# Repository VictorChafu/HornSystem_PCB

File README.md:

# HornSystem_PCB
Desarrollo de hardware en Kicad

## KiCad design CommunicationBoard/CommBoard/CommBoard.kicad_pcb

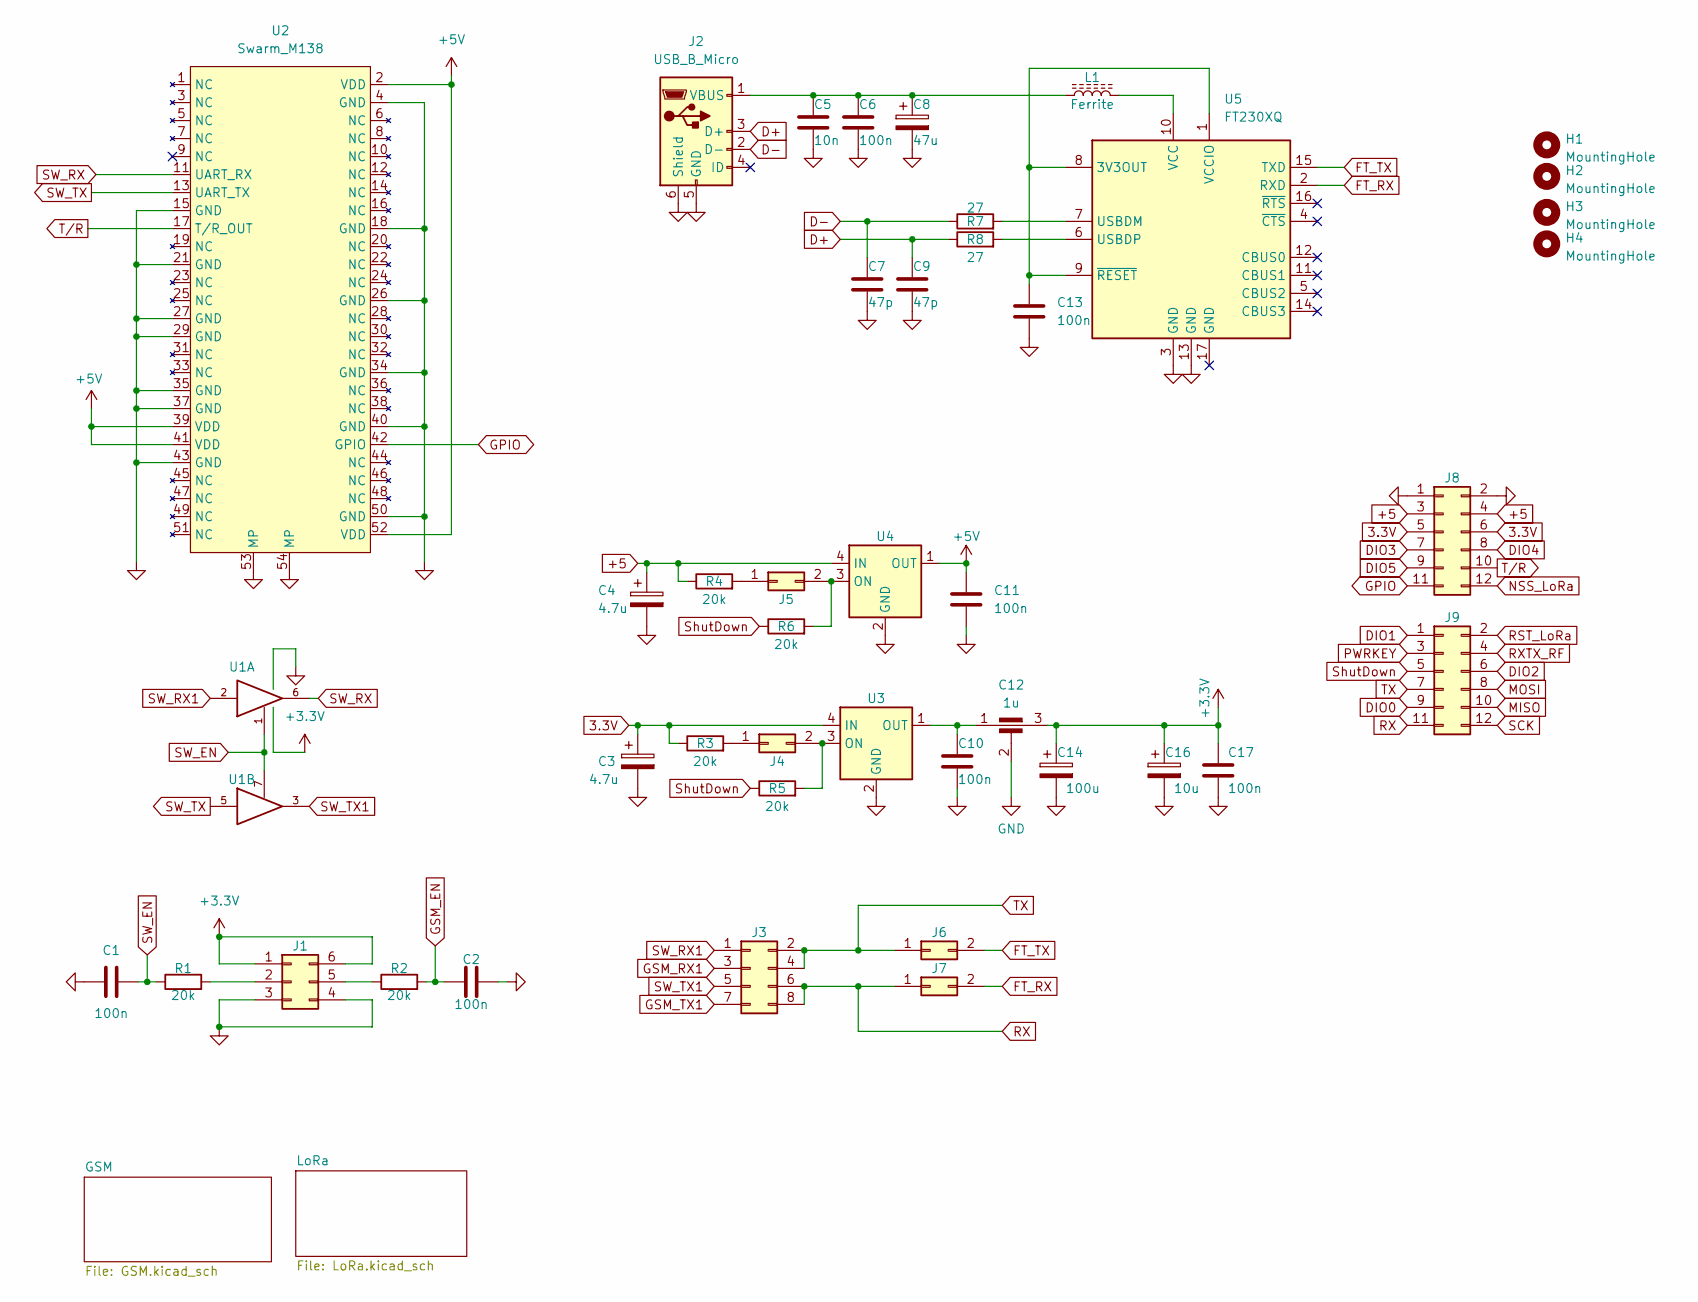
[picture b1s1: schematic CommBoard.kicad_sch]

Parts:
C1, C2, C6, C10, C11, C13, C17: 100n; C_0402_1005Metric
C3, C4: 4.7u; CP_Elec_6.3x5.2
C5: 10n; C_0402_1005Metric
C7, C9: 47p; C_0402_1005Metric
C8: 47u; CP_Elec_6.3x5.2
C12: 1u; YFF31HC
C14: 100u; CP_Elec_6.3x5.2
C16: 10u; CP_Elec_6.3x5.2
H1, H2, H3, H4: MountingHole; MountingHole_2.5mm
J1: Conn_02x03_Counter_Clockwise; PinHeader_2x03_P2.54mm_Vertical
J2: USB_B_Micro; USB_Micro-B_Molex_47346-0001
J3: Conn_02x04_Top_Bottom; PinHeader_2x04_P2.54mm_Vertical
J4, J5, J6, J7: Conn_02x01; PinHeader_2x01_P2.54mm_Vertical
J8, J9: Conn_02x06_Odd_Even; PinHeader_2x06_P2.54mm_Vertical
L1: Ferrite; L_0402_1005Metric
R1, R2, R3, R4, R5, R6: 20k; R_0402_1005Metric
R7, R8: 27; R_0402_1005Metric
U1: 74LVC2G126; VSSOP-8_2.4x2.1mm_P0.5mm
U2: Swarm_M138; BUS_PCI_Express_Mini_Dual
U3, U4: SiP35508; SOT-23-6
U5: FT230XQ; SSOP-16_3.9x4.9mm_P0.635mm

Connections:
3.3V: C3.1, J8.5, J8.6, R3.1, U3.4 (IN)
+3V3: C12.3, C14.1, C16.1, C17.1, J1.1, J1.6, U1.8 (VCC); also elsewhere on the board
+5: C4.1, J8.3, J8.4, R4.1, U4.4 (IN)
+5V: C11.1, U2.2 (VDD), U2.39 (VDD), U2.41 (VDD), U2.52 (VDD), U4.1 (OUT); also elsewhere on the board
D+: C9.1, J2.3 (D+), R8.1
D-: C7.1, J2.2 (D-), R7.1
DIO0: J9.9; also elsewhere on the board
DIO1: J9.1; also elsewhere on the board
DIO2: J9.6; also elsewhere on the board
DIO3: J8.7; also elsewhere on the board
DIO4: J8.8; also elsewhere on the board
DIO5: J8.9; also elsewhere on the board
FT_RX: J7.2, U5.2 (RXD)
FT_TX: J6.2, U5.15 (TXD)
GND: C1.1, C2.2, C3.2, C4.2, C5.2, C6.2, C7.2, C8.2, C9.2, C10.2, C11.2, C12.2, C13.2, C14.2, C16.2, C17.2, J1.3, J1.4, J2.5 (GND), J2.6 (Shield), J8.1, J8.2, U1.4 (GND), U2.4 (GND), U2.15 (GND), U2.18 (GND), U2.21 (GND), U2.26 (GND), U2.27 (GND), U2.29 (GND), U2.34 (GND), U2.35 (GND), U2.37 (GND), U2.40 (GND), U2.43 (GND), U2.50 (GND), U2.53 (MP), U2.54 (MP), U3.2 (GND), U3.5 (GND), U4.2 (GND), U4.5 (GND), U5.3 (GND), U5.13 (GND); also elsewhere on the board
GPIO: J8.11, U2.42 (GPIO)
GSM_EN: C2.1, R2.2; also elsewhere on the board
GSM_RX1: J3.3; also elsewhere on the board
GSM_TX1: J3.7; also elsewhere on the board
MISO: J9.10; also elsewhere on the board
MOSI: J9.8; also elsewhere on the board
NSS_LoRa: J8.12; also elsewhere on the board
unnamed: C5.1, C6.1, C8.1, J2.1 (VBUS), L1.1
unnamed: C10.1, C12.1, U3.1 (OUT)
unnamed: C13.1, U5.1 (VCCIO), U5.8 (3V3OUT), U5.9 (~RESET)
unnamed: J1.2, R1.2
unnamed: J1.5, R2.1
unnamed: J4.1, R3.2
unnamed: J4.2, R5.2, U3.3 (ON)
unnamed: J5.1, R4.2
unnamed: J5.2, R6.2, U4.3 (ON)
unnamed: L1.2, U5.10 (VCC)
unnamed: R7.2, U5.7 (USBDM)
unnamed: R8.2, U5.6 (USBDP)
PWRKEY: J9.3; also elsewhere on the board
RST_LoRa: J9.2; also elsewhere on the board
RX: J3.6, J3.8, J7.1, J9.11
RXTX_RF: J9.4; also elsewhere on the board
SCK: J9.12; also elsewhere on the board
SW_EN: C1.2, R1.1, U1.1, U1.7
SW_RX: U1.6, U2.11 (UART_RX)
SW_RX1: J3.1, U1.2
SW_TX: U1.5, U2.13 (UART_TX)
SW_TX1: J3.5, U1.3
ShutDown: J9.5, R5.1, R6.1
TX: J3.2, J3.4, J6.1, J9.7
T/R: J8.10, U2.17 (T/R_OUT)

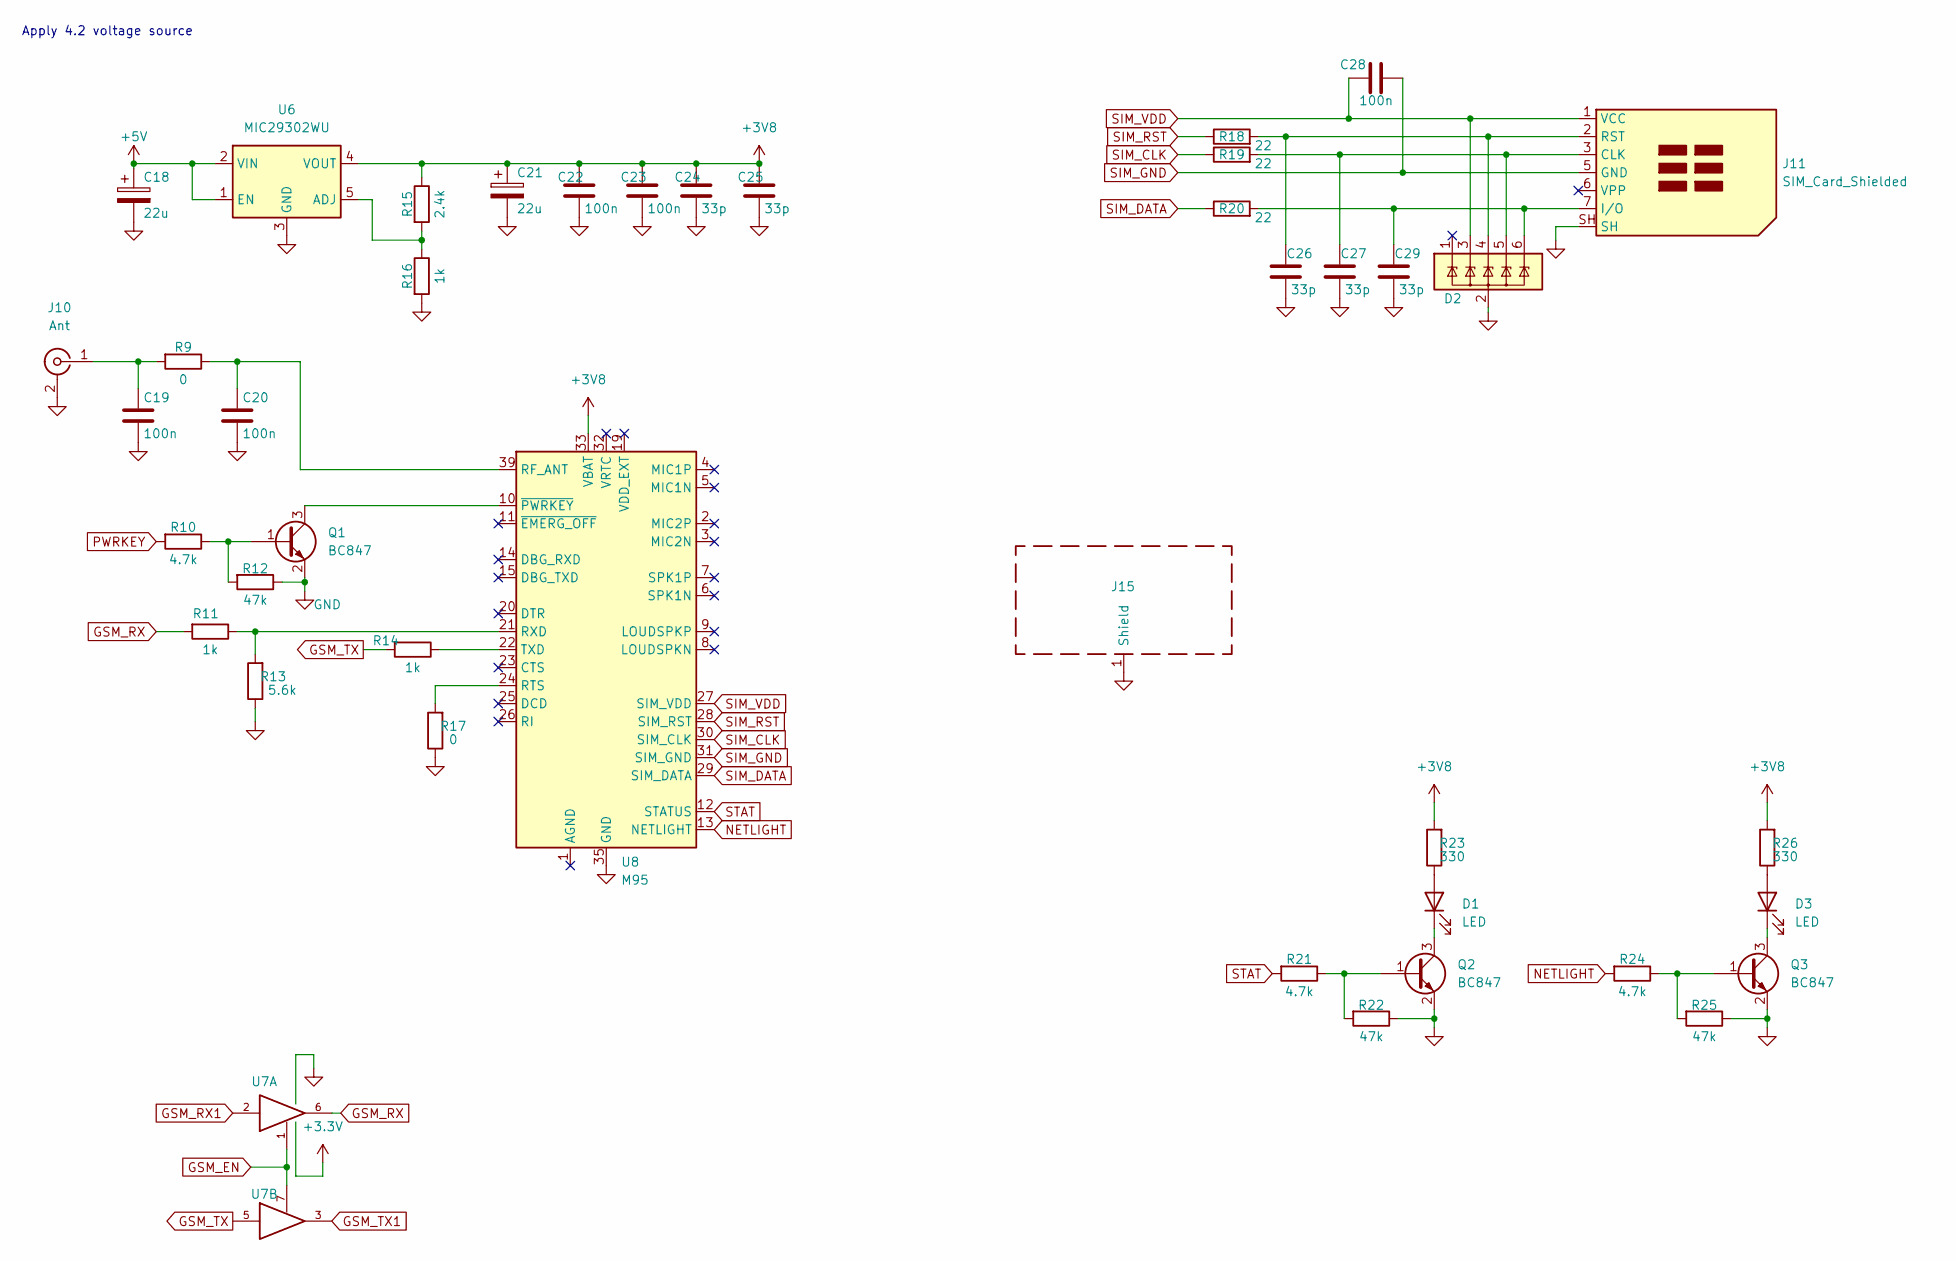
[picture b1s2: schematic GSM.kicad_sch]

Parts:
C18, C21: 22u; CP_Elec_6.3x5.2
C19, C20, C22, C23, C28: 100n; C_0402_1005Metric
C24, C25, C26, C27, C29: 33p; C_0402_1005Metric
D1, D3: LED; LED_0805_2012Metric
D2: ESDA6V1-5SC6; SOT-23-6
J10: Ant; U.FL_Hirose_U.FL-R-SMT-1_Vertical
J11: SIM_Card_Shielded; microSIM_JAE_SF53S006VCBR2000
J15: RFShield_OnePiece; Laird_Technologies_BMI-S-205-F_38.10x25.40mm
Q1, Q2, Q3: BC847; SOT-23
R9: 0; R_0402_1005Metric
R10, R21, R24: 4.7k; R_0402_1005Metric
R11, R14: 1k; R_0402_1005Metric
R12, R22, R25: 47k; R_0402_1005Metric
R13: 5.6k; R_0402_1005Metric
R15: 2.4k; R_0805_2012Metric
R16: 1k; R_0805_2012Metric
R17: 0; R_0805_2012Metric
R18, R19, R20: 22; R_0402_1005Metric
R23, R26: 330; R_0402_1005Metric
U6: MIC29302WU; TO-263-5_TabPin3
U7: 74LVC2G126; VSSOP-8_2.4x2.1mm_P0.5mm
U8: M95; Quectel_M95

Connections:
+3V3: U7.8 (VCC); also elsewhere on the board
+3V8: C21.1, C22.1, C23.1, C24.1, C25.1, R15.1, R23.2, R26.2, U6.4 (VOUT), U8.33 (VBAT), U8.34 (VBAT)
+5V: C18.1, U6.1 (EN), U6.2 (VIN); also elsewhere on the board
GND: C18.2, C19.2, C20.2, C21.2, C22.2, C23.2, C24.2, C25.2, C26.2, C27.2, C29.2, D2.2 (GND), J10.2 (Ext), J11.SH, J15.1 (Shield), Q1.2 (E), Q2.2 (E), Q3.2 (E), R12.1, R13.1, R16.2, R17.1, R22.1, R25.1, U6.3 (GND), U7.4 (GND), U8.35 (GND), U8.36 (GND), U8.37 (GND), U8.38 (GND), U8.40 (GND); also elsewhere on the board
GSM_EN: U7.1, U7.7; also elsewhere on the board
GSM_RX: R11.2, U7.6
GSM_RX1: U7.2; also elsewhere on the board
GSM_TX: R14.2, U7.5
GSM_TX1: U7.3; also elsewhere on the board
NETLIGHT: R24.2, U8.13 (NETLIGHT)
unnamed: C19.1, J10.1 (In), R9.2
unnamed: C20.1, R9.1, U8.39 (RF_ANT)
unnamed: C26.1, D2.4 (IO3), J11.2 (RST), R18.2
unnamed: C27.1, D2.5 (IO4), J11.3 (CLK), R19.2
unnamed: C29.1, D2.6 (IO5), J11.7 (I/O), R20.2
unnamed: D1.1 (K), Q2.3 (C)
unnamed: D1.2 (A), R23.1
unnamed: D3.1 (K), Q3.3 (C)
unnamed: D3.2 (A), R26.1
unnamed: Q1.1 (B), R10.1, R12.2
unnamed: Q1.3 (C), U8.10 (~PWRKEY)
unnamed: Q2.1 (B), R21.1, R22.2
unnamed: Q3.1 (B), R24.1, R25.2
unnamed: R11.1, R13.2, U8.21 (RXD)
unnamed: R14.1, U8.22 (TXD)
unnamed: R15.2, R16.1, U6.5 (ADJ)
unnamed: R17.2, U8.24 (RTS)
PWRKEY: R10.2; also elsewhere on the board
SIM_CLK: R19.1, U8.30 (SIM_CLK)
SIM_DATA: R20.1, U8.29 (SIM_DATA)
SIM_GND: C28.2, J11.5 (GND), U8.31 (SIM_GND)
SIM_RST: R18.1, U8.28 (SIM_RST)
SIM_VDD: C28.1, D2.3 (IO2), J11.1 (VCC), U8.27 (SIM_VDD)
STAT: R21.2, U8.12 (STATUS)

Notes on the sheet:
Apply 4.2 voltage source

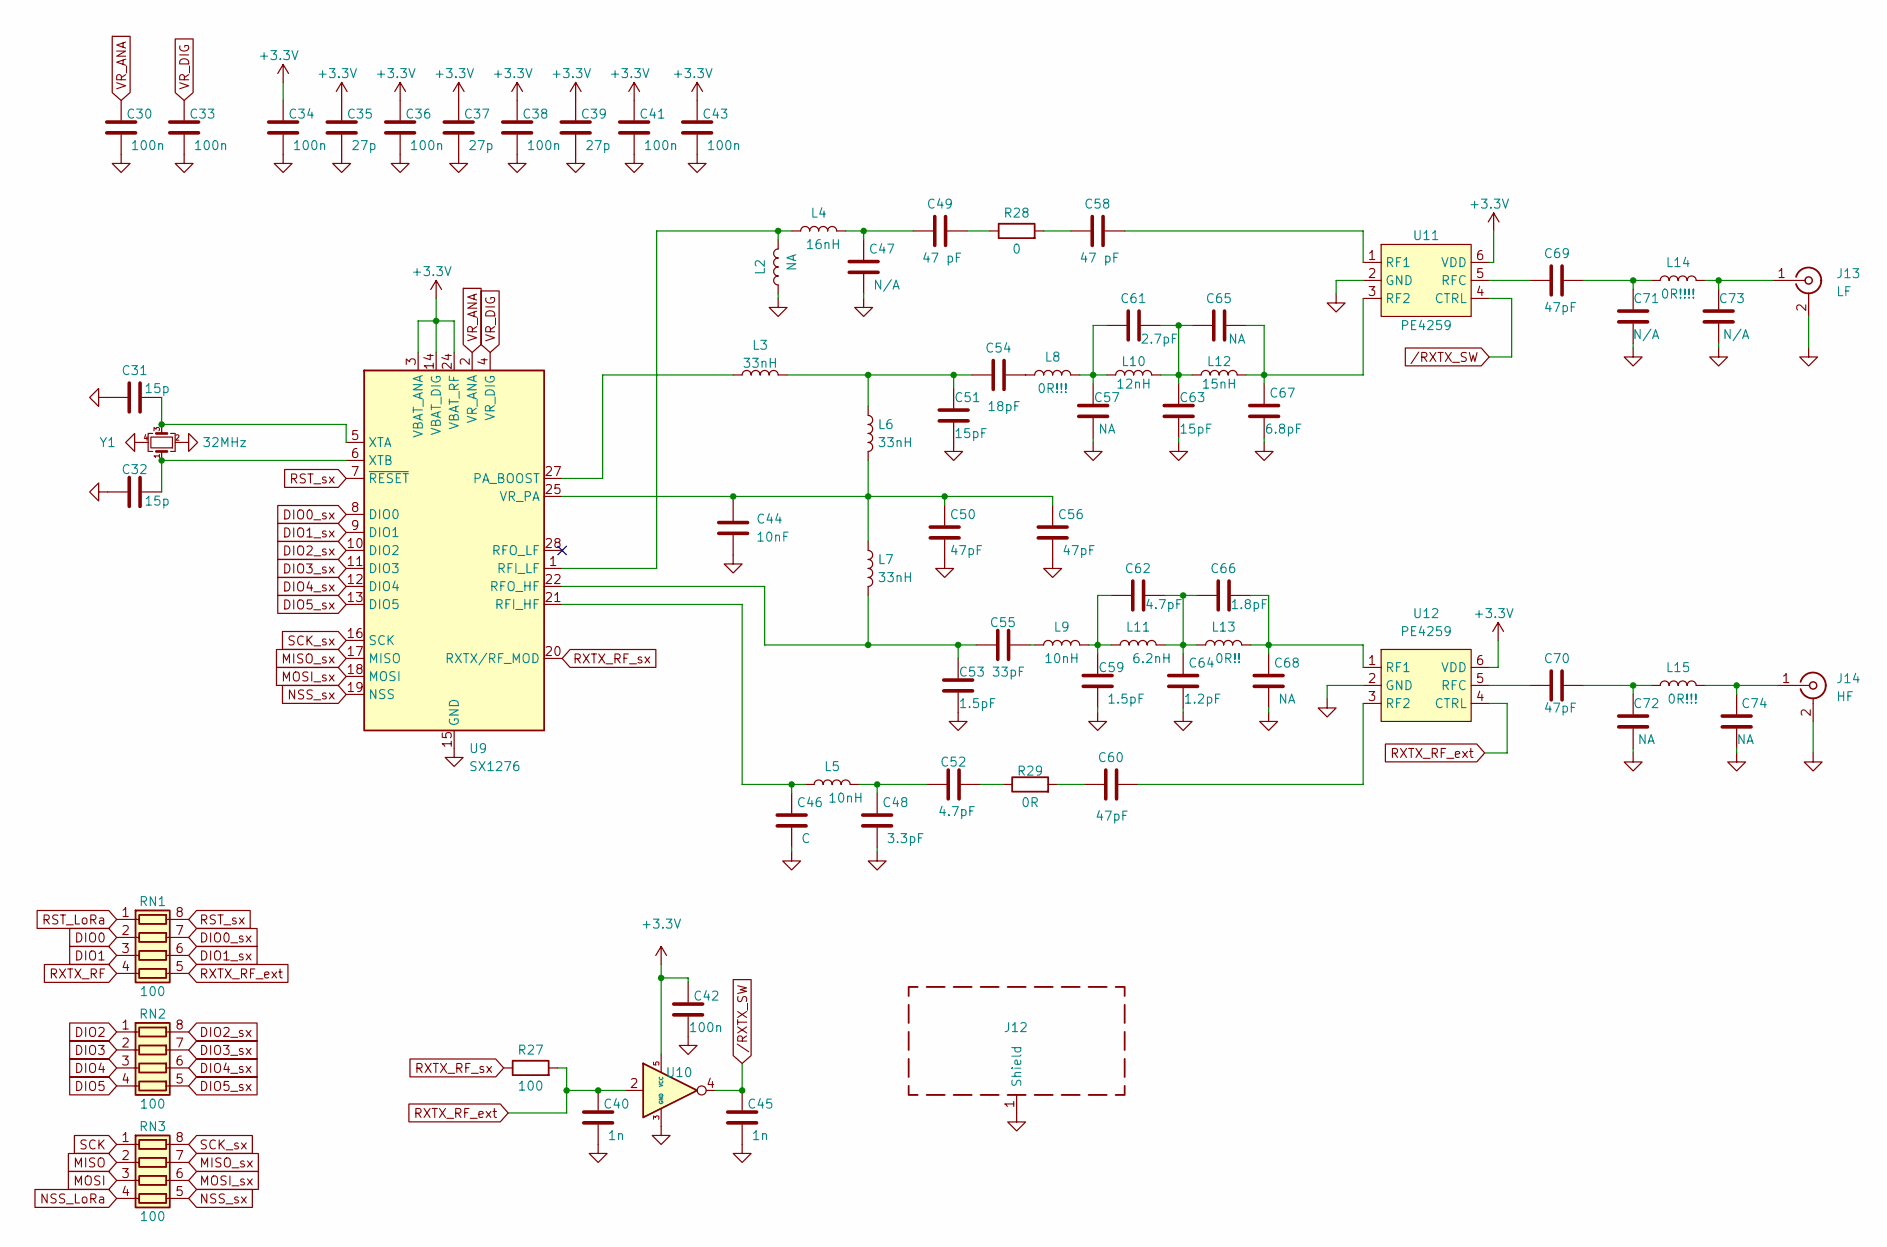
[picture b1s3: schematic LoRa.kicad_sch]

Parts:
C30, C33, C34, C36, C38, C41, C42, C43: 100n; C_0402_1005Metric
C31, C32: 15p; C_0402_1005Metric
C35, C37, C39: 27p; C_0402_1005Metric
C40, C45: 1n; C_0402_1005Metric
C44: 10nF; C_0402_1005Metric
C46: C; C_0402_1005Metric
C47, C71, C73: N/A; C_0402_1005Metric
C48: 3.3pF; C_0402_1005Metric
C49, C58: 47 pF; C_0402_1005Metric
C50, C56, C60, C69, C70: 47pF; C_0402_1005Metric
C51, C63: 15pF; C_0402_1005Metric
C52, C62: 4.7pF; C_0402_1005Metric
C53, C59: 1.5pF; C_0402_1005Metric
C54: 18pF; C_0402_1005Metric
C55: 33pF; C_0402_1005Metric
C57, C65, C68, C72, C74: NA; C_0402_1005Metric
C61: 2.7pF; C_0402_1005Metric
C64: 1.2pF; C_0402_1005Metric
C66: 1.8pF; C_0402_1005Metric
C67: 6.8pF; C_0402_1005Metric
J12: RFShield_OnePiece; Laird_Technologies_BMI-S-205-F_38.10x25.40mm
J13: LF; U.FL_Hirose_U.FL-R-SMT-1_Vertical
J14: HF; U.FL_Hirose_U.FL-R-SMT-1_Vertical
L2: NA; L_0402_1005Metric
L3, L6, L7: 33nH; L_0402_1005Metric
L4: 16nH; L_0402_1005Metric
L5, L9: 10nH; L_0402_1005Metric
L8, L15: 0R!!!; L_0402_1005Metric
L10: 12nH; L_0402_1005Metric
L11: 6.2nH; L_0402_1005Metric
L12: 15nH; L_0402_1005Metric
L13: 0R!!; L_0402_1005Metric
L14: 0R!!!!; L_0402_1005Metric
R27: 100; R_0402_1005Metric
R28: 0; R_0201_0603Metric
R29: 0R; R_0201_0603Metric_Pad0.64x0.40mm_HandSolder
RN1, RN2, RN3: 100; R_Array_Convex_4x1206
U9: SX1276; QFN-28-1EP_6x6mm_P0.65mm_EP4.8x4.8mm
U10: NC7SVU04P5X; SOT-353_SC-70-5
U11, U12: PE4259; SC70-6
Y1: 32MHz; Crystal_SMD_Abracon_ABM8G-4Pin_3.2x2.5mm

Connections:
+3V3: C34.1, C35.1, C36.1, C37.1, C38.1, C39.1, C41.1, C42.1, C43.1, U9.3 (VBAT_ANA), U9.14 (VBAT_DIG), U9.24 (VBAT_RF), U10.5 (VCC), U11.6 (VDD), U12.6 (VDD); also elsewhere on the board
DIO0: RN1.2 (R2.1); also elsewhere on the board
DIO0_sx: RN1.7 (R2.2), U9.8 (DIO0)
DIO1: RN1.3 (R3.1); also elsewhere on the board
DIO1_sx: RN1.6 (R3.2), U9.9 (DIO1)
DIO2: RN2.1 (R1.1); also elsewhere on the board
DIO2_sx: RN2.8 (R1.2), U9.10 (DIO2)
DIO3: RN2.2 (R2.1); also elsewhere on the board
DIO3_sx: RN2.7 (R2.2), U9.11 (DIO3)
DIO4: RN2.3 (R3.1); also elsewhere on the board
DIO4_sx: RN2.6 (R3.2), U9.12 (DIO4)
DIO5: RN2.4 (R4.1); also elsewhere on the board
DIO5_sx: RN2.5 (R4.2), U9.13 (DIO5)
GND: C30.2, C31.1, C32.1, C33.2, C34.2, C35.2, C36.2, C37.2, C38.2, C39.2, C40.2, C41.2, C42.2, C43.2, C44.2, C45.2, C46.2, C47.2, C48.2, C50.2, C51.2, C53.2, C56.2, C57.2, C59.2, C63.2, C64.2, C67.2, C68.2, C71.2, C72.2, C73.2, C74.2, J12.1, J13.2 (Ext), J14.2 (Ext), L2.1, U9.15 (GND), U9.23 (GND), U9.26 (GND), U9.29 (GND), U10.3 (GND), U11.2 (GND), U12.2 (GND), Y1.2, Y1.4; also elsewhere on the board
MISO: RN3.2 (R2.1); also elsewhere on the board
MISO_sx: RN3.7 (R2.2), U9.17 (MISO)
MOSI: RN3.3 (R3.1); also elsewhere on the board
MOSI_sx: RN3.6 (R3.2), U9.18 (MOSI)
NSS_LoRa: RN3.4 (R4.1); also elsewhere on the board
NSS_sx: RN3.5 (R4.2), U9.19 (NSS)
unnamed: C31.2, U9.5 (XTA), Y1.3
unnamed: C32.2, U9.6 (XTB), Y1.1
unnamed: C44.1, C50.1, C56.1, L6.2, L7.1, U9.25 (VR_PA)
unnamed: C46.1, L5.1, U9.21 (RFI_HF)
unnamed: C47.1, C49.1, L4.2
unnamed: C48.1, C52.1, L5.2
unnamed: C49.2, R28.1
unnamed: C51.1, C54.1, L3.2, L6.1
unnamed: C52.2, R29.1
unnamed: C53.1, C55.1, L7.2, U9.22 (RFO_HF)
unnamed: C54.2, L8.1
unnamed: C55.2, L9.1
unnamed: C57.1, C61.1, L8.2, L10.1
unnamed: C58.1, R28.2
unnamed: C58.2, U11.1 (RF1)
unnamed: C59.1, C62.1, L9.2, L11.1
unnamed: C60.1, R29.2
unnamed: C60.2, U12.3 (RF2)
unnamed: C61.2, C63.1, C65.1, L10.2, L12.1
unnamed: C62.2, C64.1, C66.1, L11.2, L13.1
unnamed: C65.2, C67.1, L12.2, U11.3 (RF2)
unnamed: C66.2, C68.1, L13.2, U12.1 (RF1)
unnamed: C69.1, C71.1, L14.2
unnamed: C69.2, U11.5 (RFC)
unnamed: C70.1, C72.1, L15.2
unnamed: C70.2, U12.5 (RFC)
unnamed: C73.1, J13.1 (In), L14.1
unnamed: C74.1, J14.1 (In), L15.1
unnamed: L2.2, L4.1, U9.1 (RFI_LF)
unnamed: L3.1, U9.27 (PA_BOOST)
RST_LoRa: RN1.1 (R1.1); also elsewhere on the board
RST_sx: RN1.8 (R1.2), U9.7 (~RESET)
RXTX_RF: RN1.4 (R4.1); also elsewhere on the board
RXTX_RF_ext: C40.1, R27.2, RN1.5 (R4.2), U10.2, U12.4 (CTRL)
RXTX_RF_sx: R27.1, U9.20 (RXTX/RF_MOD)
SCK: RN3.1 (R1.1); also elsewhere on the board
SCK_sx: RN3.8 (R1.2), U9.16 (SCK)
VR_ANA: C30.1, U9.2 (VR_ANA)
VR_DIG: C33.1, U9.4 (VR_DIG)
/RXTX_SW: C45.1, U10.4, U11.4 (CTRL)

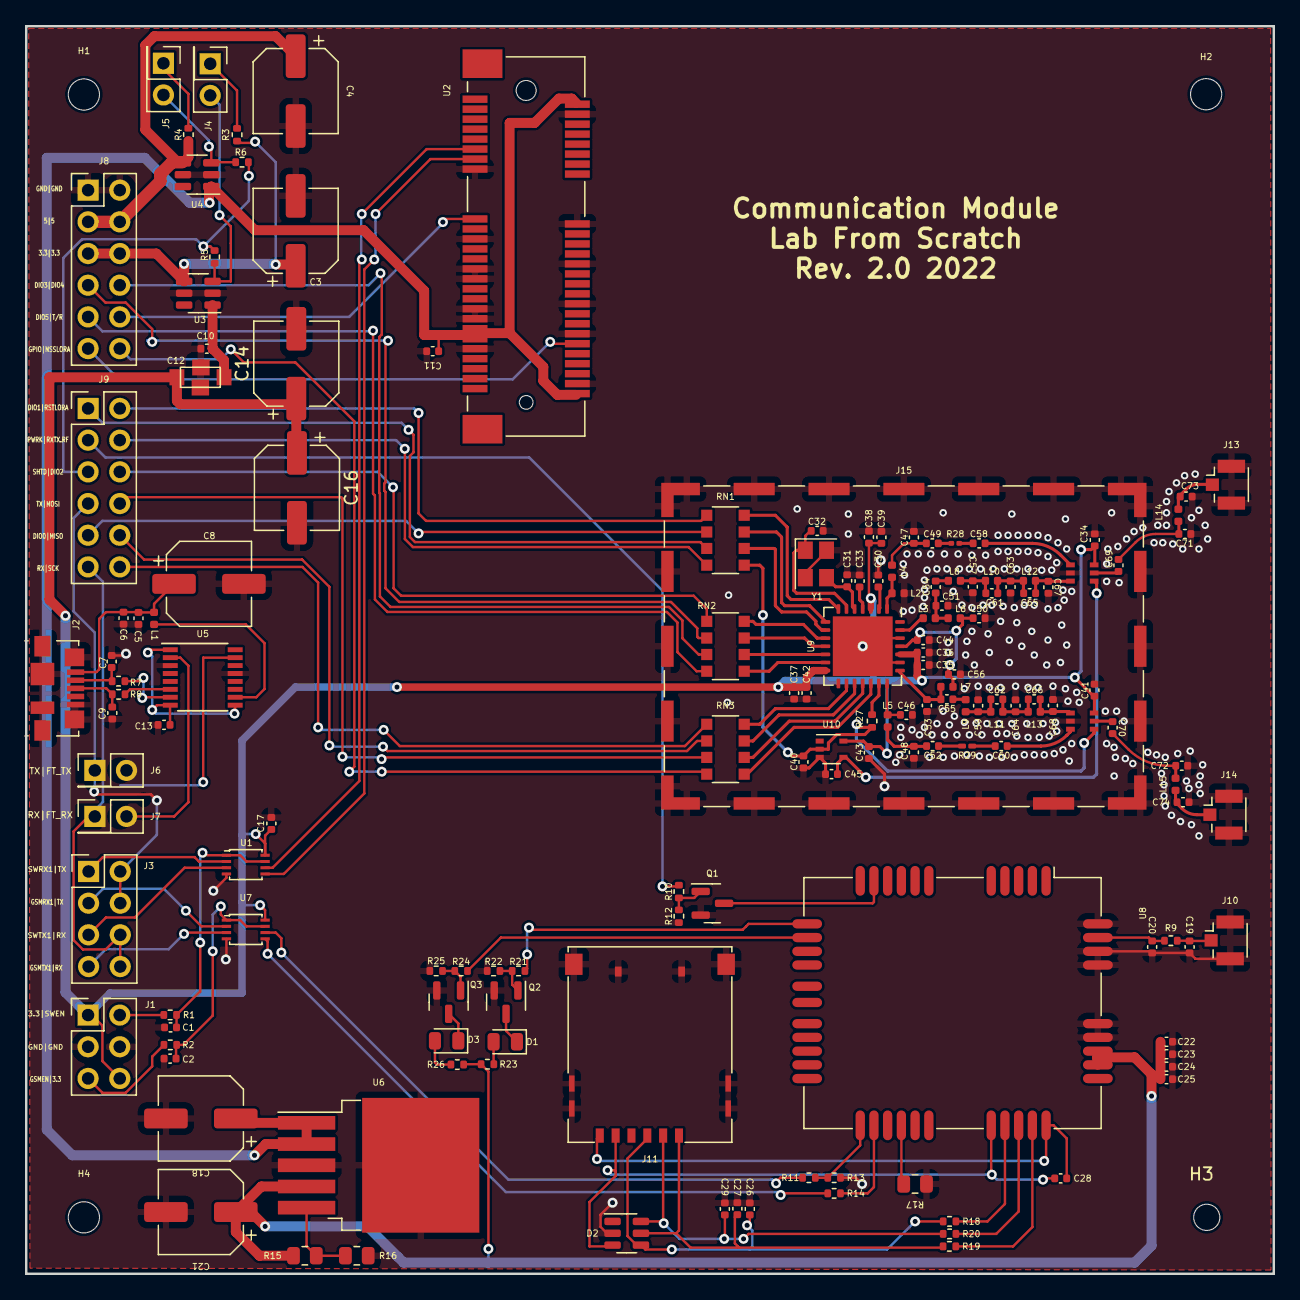
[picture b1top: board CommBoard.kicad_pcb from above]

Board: 2 copper layers, 100.0 x 100.0 mm, 157 parts (0 on the bottom side), 120 nets.

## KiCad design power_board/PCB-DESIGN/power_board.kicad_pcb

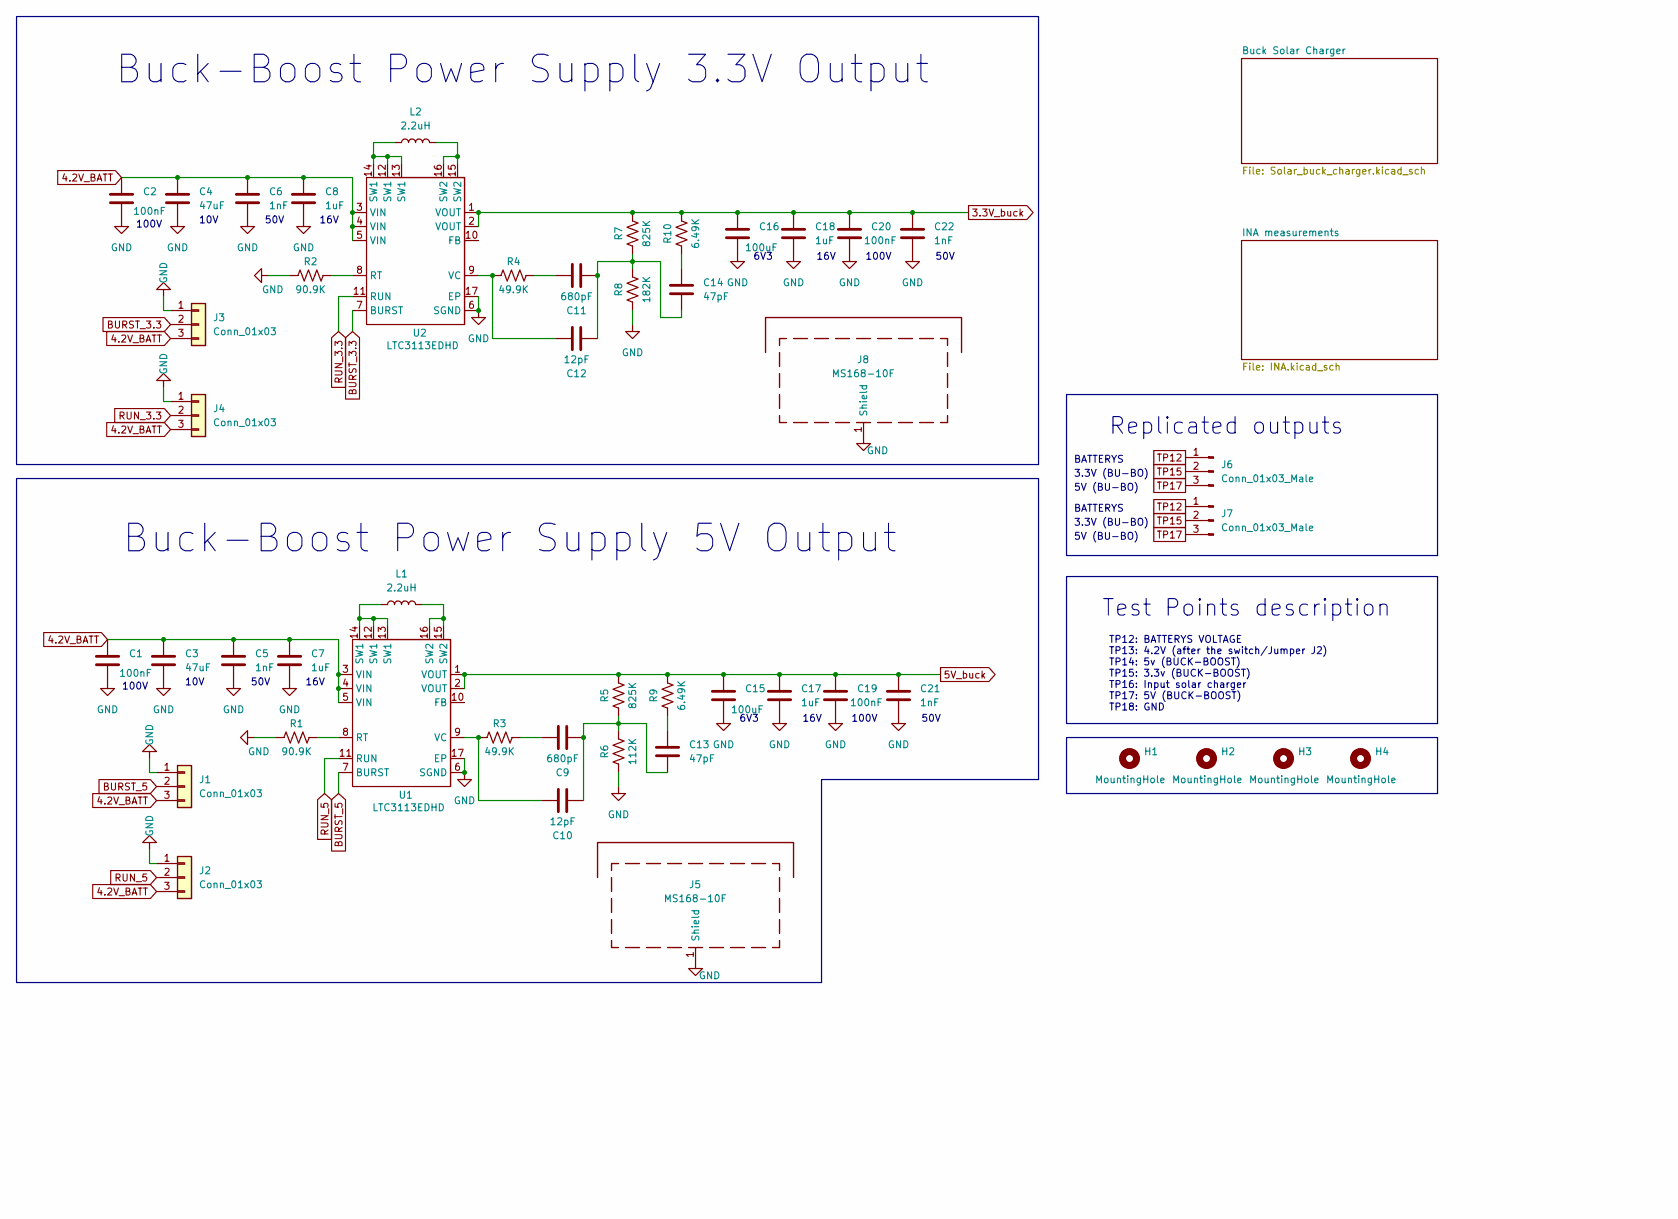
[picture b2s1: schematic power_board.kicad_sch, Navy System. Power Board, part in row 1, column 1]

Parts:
C1, C2, C19, C20: 100nF; C_0805_2012Metric
C3, C4: 47uF; C_0805_2012Metric
C5, C6, C21, C22: 1nF; C_0805_2012Metric
C7, C8, C17, C18: 1uF; C_0805_2012Metric
C9, C11: 680pF; C_0805_2012Metric
C10, C12: 12pF; C_0805_2012Metric
C13, C14: 47pF; C_0805_2012Metric
C15, C16: 100uF; C_0805_2012Metric
H1, H2, H3, H4: MountingHole; MountingHole_2.5mm
J1, J2, J3, J4: Conn_01x03; PinHeader_1x03_P2.54mm_Vertical
J5, J8: MS168-10F; Wuerth_36103205_20x20mm
J6, J7: Conn_01x03_Male; PinHeader_1x03_P2.54mm_Vertical
L1, L2: 2.2uH; L_Vishay_IHLP-2525
R1, R2: 90.9K; R_0805_2012Metric
R3, R4: 49.9K; R_0805_2012Metric
R5, R7: 825K; R_0805_2012Metric
R6: 112K; R_0805_2012Metric
R8: 182K; R_0805_2012Metric
R9, R10: 6.49K; R_0805_2012Metric
U1, U2: LTC3113EDHD; SSOP-20_4.4x6.5mm_P0.65mm

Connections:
3.3V_buck: C16.1, C18.1, C20.1, C22.1, R7.1, R10.1, U2.1 (VOUT), U2.2 (VOUT); also elsewhere on the board
4.2V_BATT: C1.1, C2.1, C3.1, C4.1, C5.1, C6.1, C7.1, C8.1, J1.3, J2.3, J3.3, J4.3, J6.1, J7.1, U1.3 (VIN), U1.4 (VIN), U1.5 (VIN), U2.3 (VIN), U2.4 (VIN), U2.5 (VIN); also elsewhere on the board
5V_buck: C15.1, C17.1, C19.1, C21.1, R5.1, R9.1, U1.1 (VOUT), U1.2 (VOUT); also elsewhere on the board
BURST_3.3: J3.2, U2.7 (BURST)
BURST_5: J1.2, U1.7 (BURST)
GND: C1.2, C2.2, C3.2, C4.2, C5.2, C6.2, C7.2, C8.2, C15.2, C16.2, C17.2, C18.2, C19.2, C20.2, C21.2, C22.2, J1.1, J2.1, J3.1, J4.1, J5.1 (Shield), J8.1 (Shield), R1.2, R2.2, R6.2, R8.2, U1.6 (SGND), U1.17 (EP), U2.6 (SGND), U2.17 (EP); also elsewhere on the board
unnamed: C9.2, R3.1
unnamed: C9.1, C10.1, C13.2, R5.2, R6.1
unnamed: C10.2, R3.2, U1.9 (VC)
unnamed: C11.1, C12.1, C14.2, R7.2, R8.1
unnamed: C11.2, R4.1
unnamed: C12.2, R4.2, U2.9 (VC)
unnamed: C13.1, R9.2
unnamed: C14.1, R10.2
unnamed: L1.1, U1.12 (SW1), U1.13 (SW1), U1.14 (SW1)
unnamed: L1.2, U1.15 (SW2), U1.16 (SW2)
unnamed: L2.1, U2.12 (SW1), U2.13 (SW1), U2.14 (SW1)
unnamed: L2.2, U2.15 (SW2), U2.16 (SW2)
unnamed: R1.1, U1.8 (RT)
unnamed: R2.1, U2.8 (RT)
RUN_3.3: J4.2, U2.11 (RUN)
RUN_5: J2.2, U1.11 (RUN)
TP15: J6.2, J7.2
TP17: J6.3, J7.3

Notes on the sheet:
16V
100V
TP12: BATTERYS VOLTAGE TP13: 4.2V (after the switch/Jumper J2) TP14: 5v (BUCK-BOOST) TP15: 3.3v (BUCK-BOOST) TP16: Input solar charger TP17: 5V (BUCK-BOOST) TP18: GND
3.3V (BU-BO)
50V
Buck-Boost Power Supply 3.3V Output
5V (BU-BO)
6V3
Buck-Boost Power Supply 5V Output
BATTERYS
10V
Replicated outputs
Test Points description

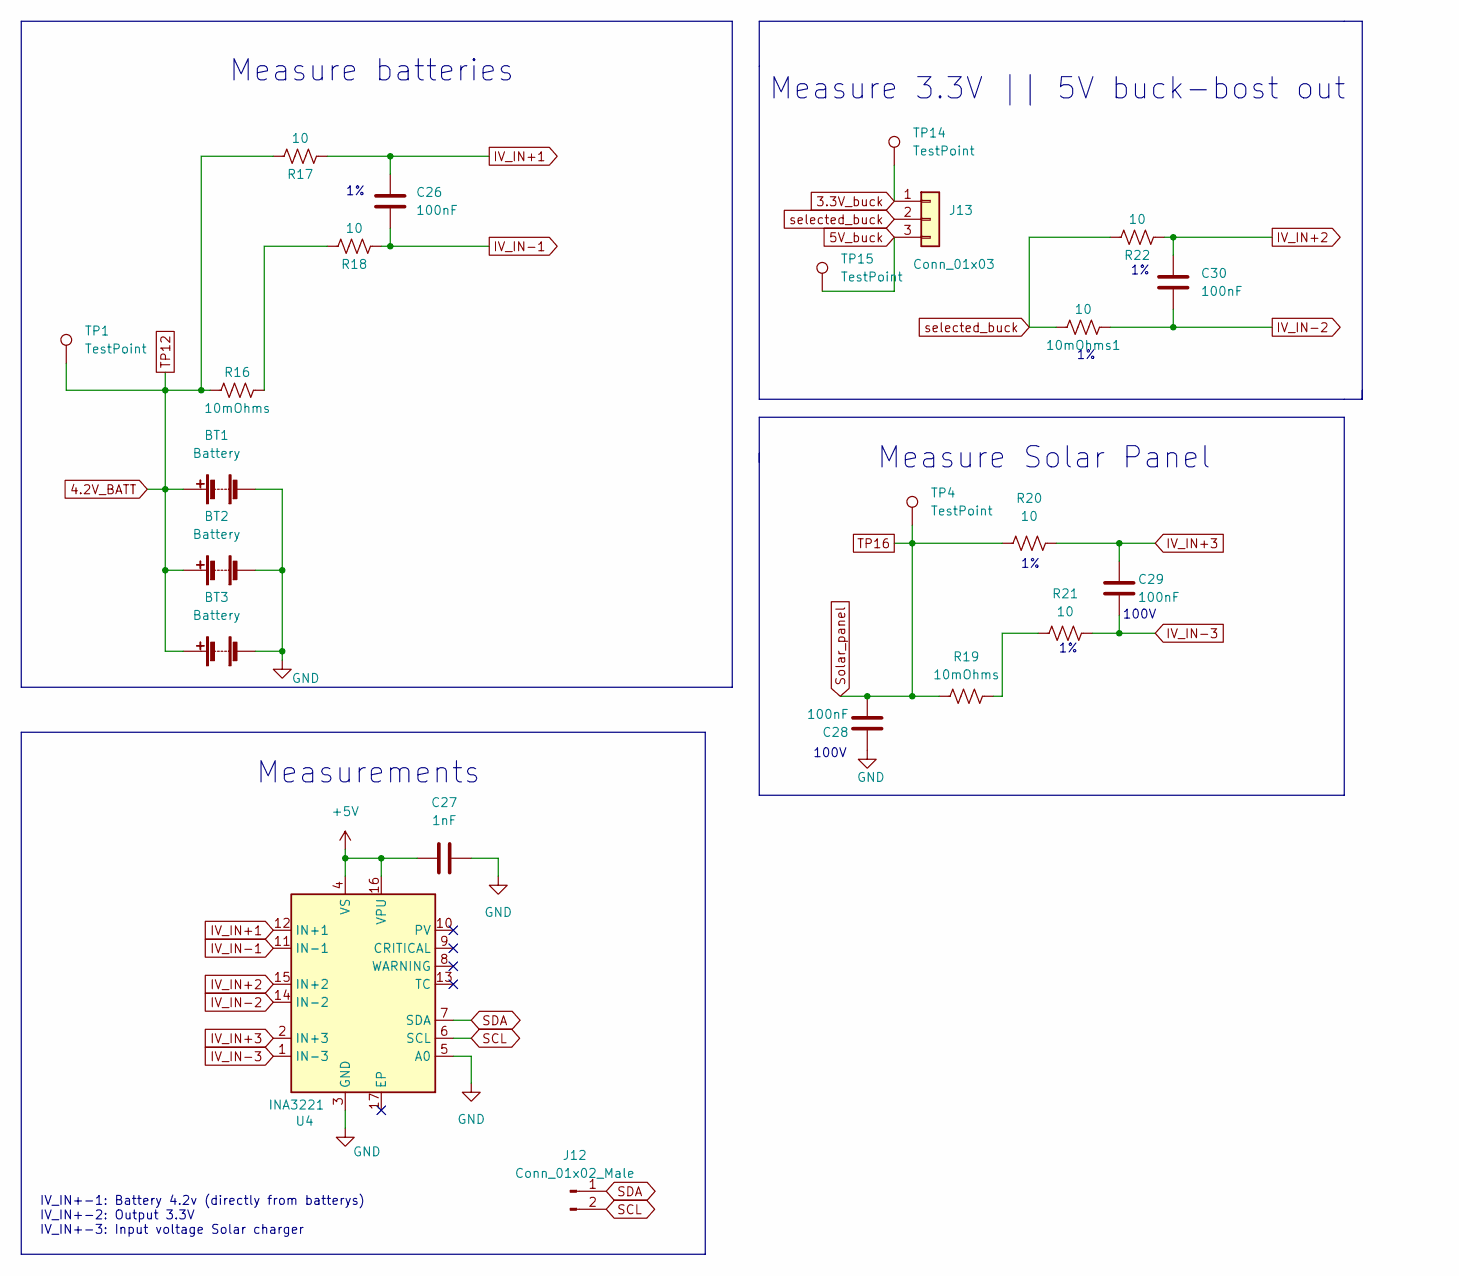
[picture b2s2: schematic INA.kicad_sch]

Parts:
10mOhms1: 10; R_0805_2012Metric
BT1, BT2, BT3: Battery; BatteryHolder_MPD_BH-18650-PC2
C26, C28, C29, C30: 100nF; C_0805_2012Metric
C27: 1nF; C_0805_2012Metric
J12: Conn_01x02_Male; PinHeader_1x02_P2.54mm_Vertical
J13: Conn_01x03; PinHeader_1x03_P2.54mm_Vertical
R16, R19: 10mOhms; R_0805_2012Metric
R17, R18, R20, R21, R22: 10; R_0805_2012Metric
TP1, TP4, TP14, TP15: TestPoint; TestPoint_Loop_D2.54mm_Drill1.5mm_Beaded
U4: INA3221; Texas_RGV_S-PVQFN-N16_EP2.1x2.1mm

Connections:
3.3V_buck: J13.1, TP14.1; also elsewhere on the board
4.2V_BATT: BT1.1 (+), BT2.1 (+), BT3.1 (+), R16.1, R17.1, TP1.1; also elsewhere on the board
5V_buck: J13.3, TP15.1; also elsewhere on the board
+5V: C27.1, U4.4 (VS), U4.16 (VPU)
GND: BT1.2 (-), BT2.2 (-), BT3.2 (-), C27.2, C28.1, U4.3 (GND), U4.5 (A0); also elsewhere on the board
IV_IN+1: C26.1, R17.2, U4.12 (IN+1)
IV_IN+2: C30.1, R22.2, U4.15 (IN+2)
IV_IN+3: C29.1, R20.1, U4.2 (IN+3)
IV_IN-1: C26.2, R18.2, U4.11 (IN-1)
IV_IN-2: 10mOhms1.2, C30.2, U4.14 (IN-2)
IV_IN-3: C29.2, R21.1, U4.1 (IN-3)
unnamed: R16.2, R18.1
unnamed: R19.1, R21.2
SCL: J12.2, U4.6 (SCL)
SDA: J12.1, U4.7 (SDA)
Solar_panel: C28.2, R19.2, R20.2, TP4.1; also elsewhere on the board
selected_buck: 10mOhms1.1, J13.2, R22.1

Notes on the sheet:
100V
Measure Solar Panel
Measurements
IV_IN+-1: Battery 4.2v (directly from batterys) IV_IN+-2: Output 3.3V IV_IN+-3: Input voltage Solar charger
Measure batteries
Measure 3.3V || 5V buck-bost out

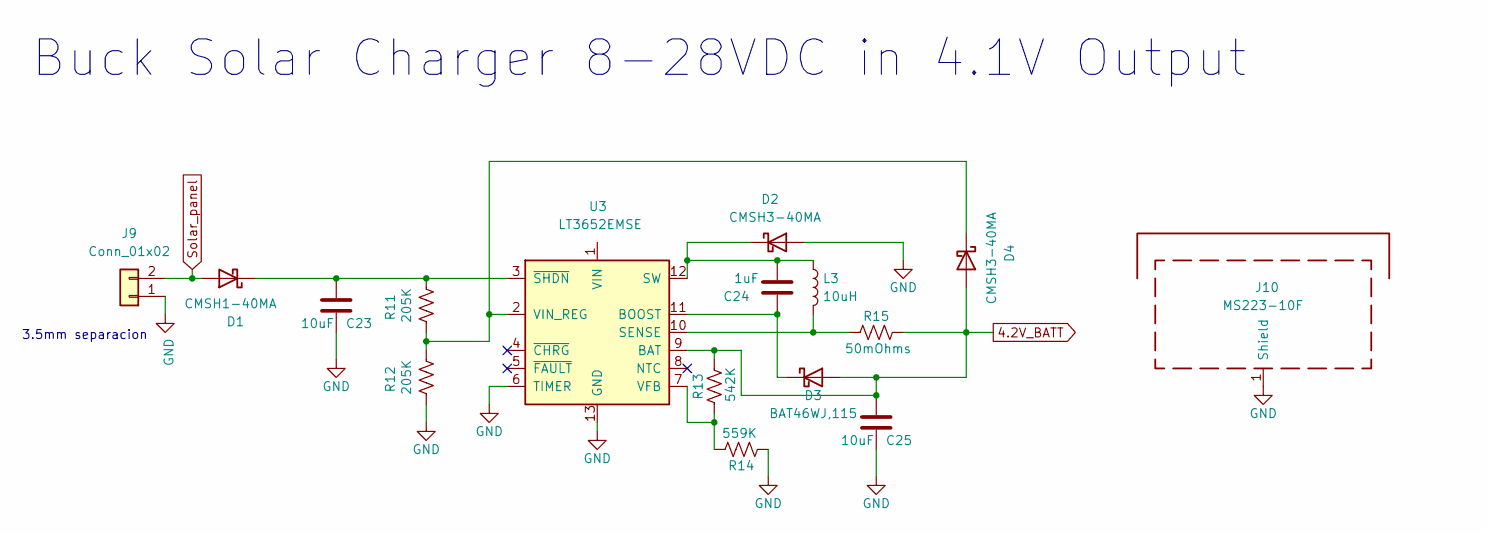
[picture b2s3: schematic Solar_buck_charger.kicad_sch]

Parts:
C23, C25: 10uF; C_0805_2012Metric
C24: 1uF; C_0805_2012Metric
D1: CMSH1-40MA; D_SOD-128
D2, D4: CMSH3-40MA; D_SOD-128
D3: BAT46WJ,115; D_SOD-323F
J9: Conn_01x02; TerminalBlock_Phoenix_PT-1,5-2-3.5-H_1x02_P3.50mm_Horizontal
J10: MS223-10F; Wuerth_36103255_25x25mm
L3: 10uH; L_Vishay_IHLP-2525
R11, R12: 205K; R_0805_2012Metric
R13: 542K; R_0805_2012Metric
R14: 559K; R_0805_2012Metric
R15: 50mOhms; R_0805_2012Metric
U3: LT3652EMSE; MSOP-12-1EP_3x4mm_P0.65mm_EP1.65x2.85mm

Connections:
4.2V_BATT: C25.1, D3.2 (A), D4.2 (A), R13.1, R15.1, U3.9 (BAT); also elsewhere on the board
GND: C23.2, C25.2, D2.2 (A), J9.1, J10.1 (Shield), R12.1, R14.2, U3.6 (TIMER), U3.13 (GND); also elsewhere on the board
unnamed: C23.1, D1.1 (K), R11.2, U3.3 (~SHDN)
unnamed: C24.1, D3.1 (K), U3.11 (BOOST)
unnamed: C24.2, D2.1 (K), L3.1, U3.12 (SW)
unnamed: D4.1 (K), R11.1, R12.2, U3.2 (VIN_REG)
unnamed: L3.2, R15.2, U3.10 (SENSE)
unnamed: R13.2, R14.1, U3.7 (VFB)
Solar_panel: D1.2 (A), J9.2; also elsewhere on the board

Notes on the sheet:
Buck Solar Charger 8-28VDC in 4.1V Output
3.5mm separacion
